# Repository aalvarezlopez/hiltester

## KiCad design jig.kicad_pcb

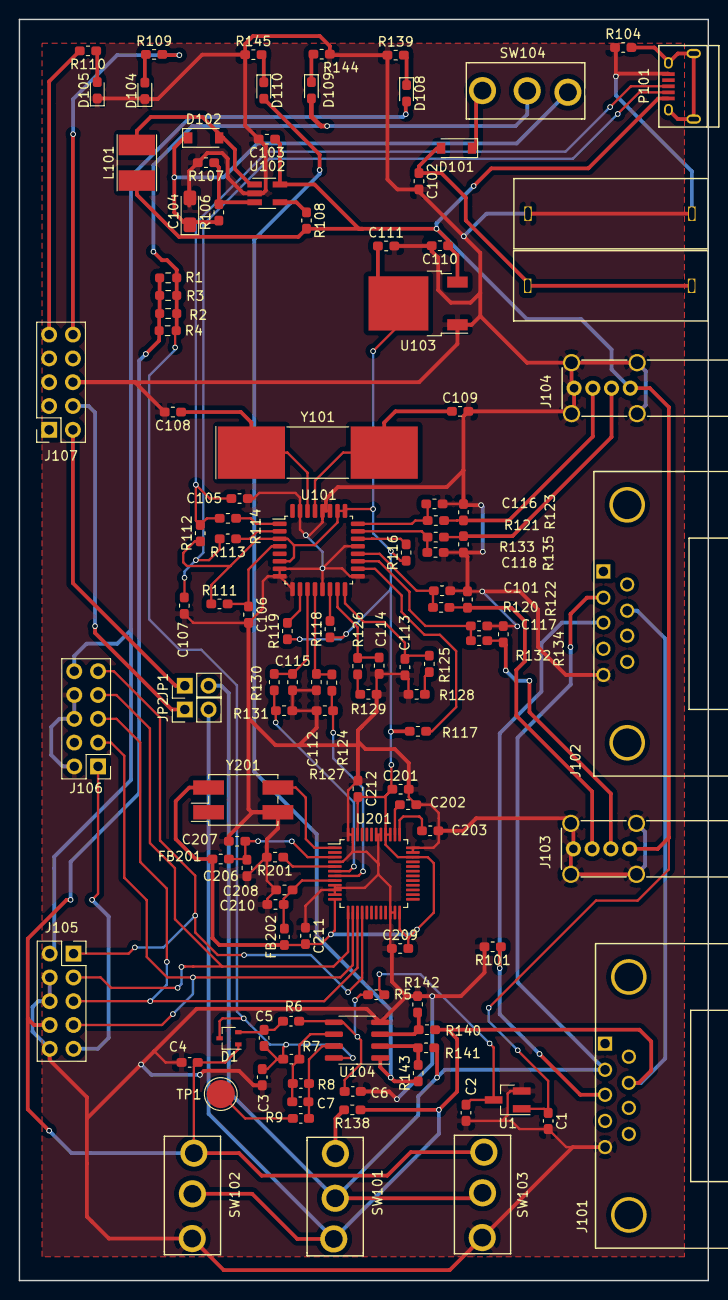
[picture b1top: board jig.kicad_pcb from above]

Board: 2 copper layers, 73.5 x 134.6 mm, 120 parts (0 on the bottom side), 73 nets.

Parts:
C1, C2: 1u; C_0603_1608Metric_Pad1.08x0.95mm_HandSolder
C3, C4: 10n; C_0603_1608Metric_Pad1.08x0.95mm_HandSolder
C5: 1n; C_0603_1608Metric_Pad1.08x0.95mm_HandSolder
C6, C7: 100p; C_0603_1608Metric_Pad1.08x0.95mm_HandSolder
C101, C105, C107, C108, C109, C112, C113, C114, C115, C116, C117, C118: 22p; C_0603_1608Metric_Pad1.05x0.95mm_HandSolder
C102, C201, C202, C203: C; C_0603_1608Metric_Pad1.05x0.95mm_HandSolder
C103, C110, C111: 10u; C_0603_1608Metric_Pad1.05x0.95mm_HandSolder
C104: 10u; CP_EIA-3216-10_Kemet-I_Pad1.58x1.35mm_HandSolder
C106, C206, C208: 4.7u; C_0603_1608Metric_Pad1.05x0.95mm_HandSolder
C207, C209, C210, C211, C212: 100n; C_0603_1608Metric_Pad1.05x0.95mm_HandSolder
D1: BAT54SW; SOT-323_SC-70
D101, D102: D_Schottky; D_SOD-123
D104, D105, D108, D109, D110: LED; D_0603_1608Metric_Pad1.05x0.95mm_HandSolder
FB201, FB202: FILTER; R_0603_1608Metric_Pad1.05x0.95mm_HandSolder
J101, J102: DB9; DB9FC
J103, J104: USB_A; USB_A_Vertical
J105, J107: Conn_02x05_Odd_Even; PinSocket_2x05_P2.54mm_Vertical
J106: Conn_02x05_Odd_Even; PinHeader_2x05_P2.54mm_Vertical
JP1, JP2: Jumper; PinHeader_1x02_P2.54mm_Vertical
L101: 4.7u; L_Taiyo-Yuden_NR-40xx_HandSoldering
P101: USB_OTG; USB_Micro-B
P102: RED_JACK; 4mm_Banana_Plug
P103: BLACK_JACK; 4mm_Banana_Plug
R1, R2, R3, R4: 4m; R_0603_1608Metric_Pad0.98x0.95mm_HandSolder
R5, R8: 162k; C_0603_1608Metric_Pad1.08x0.95mm_HandSolder
R6, R7: 2k55; C_0603_1608Metric_Pad1.08x0.95mm_HandSolder
R9: 0; C_0603_1608Metric_Pad1.08x0.95mm_HandSolder
R101, R109, R110, R139, R144, R145: R; R_0603_1608Metric_Pad1.05x0.95mm_HandSolder
R104: 0; R_0603_1608Metric_Pad1.05x0.95mm_HandSolder
R106: 1.05M; R_0603_1608Metric_Pad1.05x0.95mm_HandSolder
R107: 120k; R_0603_1608Metric_Pad1.05x0.95mm_HandSolder
R108: 1M; R_0603_1608Metric_Pad1.05x0.95mm_HandSolder
R111, R122, R123, R127, R128, R129, R131, R134, R135: 15k; R_0603_1608Metric_Pad1.05x0.95mm_HandSolder
R112: 1.5k; R_0603_1608Metric_Pad1.05x0.95mm_HandSolder
R113, R114, R120, R121, R124, R125, R126, R130, R132, R133: 27; R_0603_1608Metric_Pad1.05x0.95mm_HandSolder
R116, R117, R118, R119, R140, R141: 10k; R_0603_1608Metric_Pad1.05x0.95mm_HandSolder
R138: 120; R_0603_1608Metric_Pad1.05x0.95mm_HandSolder
R142, R143: 20k; R_0603_1608Metric_Pad1.05x0.95mm_HandSolder
R201: 12k; R_0603_1608Metric_Pad1.05x0.95mm_HandSolder
SW101, SW102, SW103, SW104: SW_Push_SPDT; SPDT_PCB_SWITCH
TP1: TestPoint; TestPoint_Pad_D3.0mm
U1: AP7361C-25E; SOT-23_Handsoldering
U101: TUSB2046B; LQFP-32_7x7mm_P0.8mm
U102: MCP1661; SOT-23-5_HandSoldering
U103: ZLDO1117K33TC; TO-252-2
U104: LM358; SOIC-8_3.9x4.9mm_P1.27mm
U201: FT232H; LQFP-48_7x7mm_P0.5mm
Y101: 6Mhz; Crystal_SMD_SeikoEpson_MA505-2Pin_12.7x5.1mm_HandSoldering
Y201: Crystal_GND24; Crystal_SMD_EuroQuartz_MQ-4Pin_7.0x5.0mm_HandSoldering

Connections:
+2V5: C2.1, R5.2, U1.3
+5V: C1.1, C103.1, C110.1, J103.1, J104.1, L101.1, P101.1, R108.2, U1.1, U102.5, U103.3
+12V: C4.1, D1.1, J105.8, R1.1, R2.1, R3.1, R4.1, SW102.1, SW103.1
/12_input: C102.1, D101.2, P102.1, P102.2
/CANGND: J101.3, J102.3, R101.1
/CANH: J101.7, J102.7, JP2.2, R138.1, R140.1, SW101.1, SW102.2
/CANL: J101.2, J102.2, JP1.2, R141.2, SW101.2, SW103.2
/CAN_dm: R126.1, R129.1
/CAN_dp: R125.1, R128.1
/EXTUSB1_dm: J103.2, R132.1, R134.1
/EXTUSB1_dp: J103.3, R120.1, R122.1
/EXTUSB2_dm: J104.2, R133.1, R135.1
/EXTUSB2_dp: J104.3, R121.1, R123.1
/JTAG_dm: R130.1, R131.1, U201.6
/JTAG_dp: R124.1, R127.1, U201.7
/TCK: J105.3, J106.7, U201.13
/TDI: J105.7, J106.3, U201.14
/TDO: J105.5, J106.5, U201.15
/TMS: J105.1, J106.9, U201.16
/USB_DM: C107.1, P101.2, R113.2
/USB_DP: C105.1, P101.3, R112.2, R114.2
/XTAL1: C108.1, U101.30, Y101.1
/XTAL2: C109.1, U101.29, Y101.2
/dm1: C115.1, R130.2, U101.11
/dm2: C114.1, R126.2, U101.15
/dm3: C117.1, R132.2, U101.19
/dm4: C118.1, R133.2, U101.23
/dp1: C112.1, R124.2, U101.12
/dp2: C113.1, R125.2, U101.16
/dp3: C101.1, R120.2, U101.20
/dp4: C116.1, R121.2, U101.24
/sense-: C3.1, C5.2, D1.3, D109.2, R1.2, R2.2, R3.2, R4.2, R7.2, SW104.2, U104.8
/uC_reset: J105.9, J106.1
/vref_uC: D108.2, J105.2, J106.10
GND: C1.2, C2.2, C3.2, C4.2, C6.2, C101.2, C102.2, C103.2, C104.2, C105.2, C106.2, C107.2, C108.2, C109.2, C110.2, C111.2, C112.2, C113.2, C114.2, C115.2, C116.2, C117.2, C118.2, C201.2, C202.2, C203.2, C206.2, C207.2, C208.1, C209.1, C210.1, C211.1, C212.1, D104.1, D105.1, J101.5, J102.5, J103.4, J103.5, J104.4, J104.5, J105.4, J105.6, J105.10, J106.2, J106.6, J106.8, J107.6, P101.5, P103.1, P103.2, R101.2, R104.1, R107.2, R122.2, R123.2, R127.2, R128.2, R129.2, R131.2, R134.2, R135.2, R139.1, R142.2, R144.1, R145.1, R201.2, SW102.3, SW103.3, U1.2, U101.7, U101.8, U101.9, U101.13, U101.17, U101.21, U101.27, U101.28, U101.31, U102.2, U103.1, U104.4, U201.4, U201.9, U201.10, U201.11, U201.22, U201.23, U201.35, U201.36, U201.41, U201.42, U201.47, U201.48, Y201.2
unnamed: C5.1, D1.2, R6.2
unnamed: C6.1, R5.1, R6.1, U104.5
unnamed: C7.1, R8.1, R9.2, U104.7
unnamed: C7.2, R7.1, R8.2, U104.6
unnamed: C104.1, D102.1, R106.1, SW104.1
unnamed: C106.1, R111.2, U101.4
unnamed: C202.1, U201.38
unnamed: C203.1, U201.37
unnamed: C206.1, C207.1, FB201.2, U201.3
unnamed: C208.2, C210.2, FB202.2, U201.8
unnamed: D101.1, SW104.3
unnamed: D102.2, L101.2, U102.1
unnamed: D104.2, R109.1
unnamed: D105.2, R110.1
unnamed: D108.1, R139.2
unnamed: D109.1, R144.2
unnamed: D110.1, R145.2
unnamed: D110.2, R143.1, U104.1
unnamed: J107.2, JP1.1
unnamed: J107.4, JP2.1
unnamed: J107.9, R110.2
unnamed: J107.10, R109.2
unnamed: P101.6, R104.2
unnamed: R9.1, TP1.1
unnamed: R106.2, R107.1, U102.3
unnamed: R108.1, U102.4
unnamed: R113.1, U101.2
unnamed: R114.1, U101.1
unnamed: R116.2, U101.22
unnamed: R117.2, U101.18
unnamed: R118.2, U101.14
unnamed: R119.2, U101.10
unnamed: R138.2, SW101.3
unnamed: R140.2, R142.1, U104.3
unnamed: R141.1, R143.2, U104.2
unnamed: R201.1, U201.5
unnamed: U201.1, Y201.3
VCC: C111.1, C201.1, C209.2, C211.2, C212.2, FB201.1, FB202.1, R111.1, R112.1, R116.1, R117.1, R118.1, R119.1, U101.3, U101.6, U101.25, U101.26, U103.2, U201.12, U201.24, U201.34, U201.39, U201.40, U201.46, Y201.4

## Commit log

2024-03-20 Init
